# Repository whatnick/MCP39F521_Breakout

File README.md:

# MCP39F521 Breakout PCB

This is a basic breakout PCB for the [MCP39F521](https://www.microchip.com/wwwproducts/en/MCP39F521)
ASIC from Microchip. This ASIC has ADC's and an embedded PIC microcontroller to perform high-accuracy
energy measurements. The ASIC can appear in upto 4 i2c addresses based on jumper settings. The breakout
board is usable with this [Arduino Library](https://github.com/upbeatlabs/drwattson/tree/master/Arduino/UpbeatLabs_MCP39F521)

## PCB Design

## PCB Availabilty

- [Tindie]()
- [PCBWay]()
- [Aisler]()
- [OSHPark]()

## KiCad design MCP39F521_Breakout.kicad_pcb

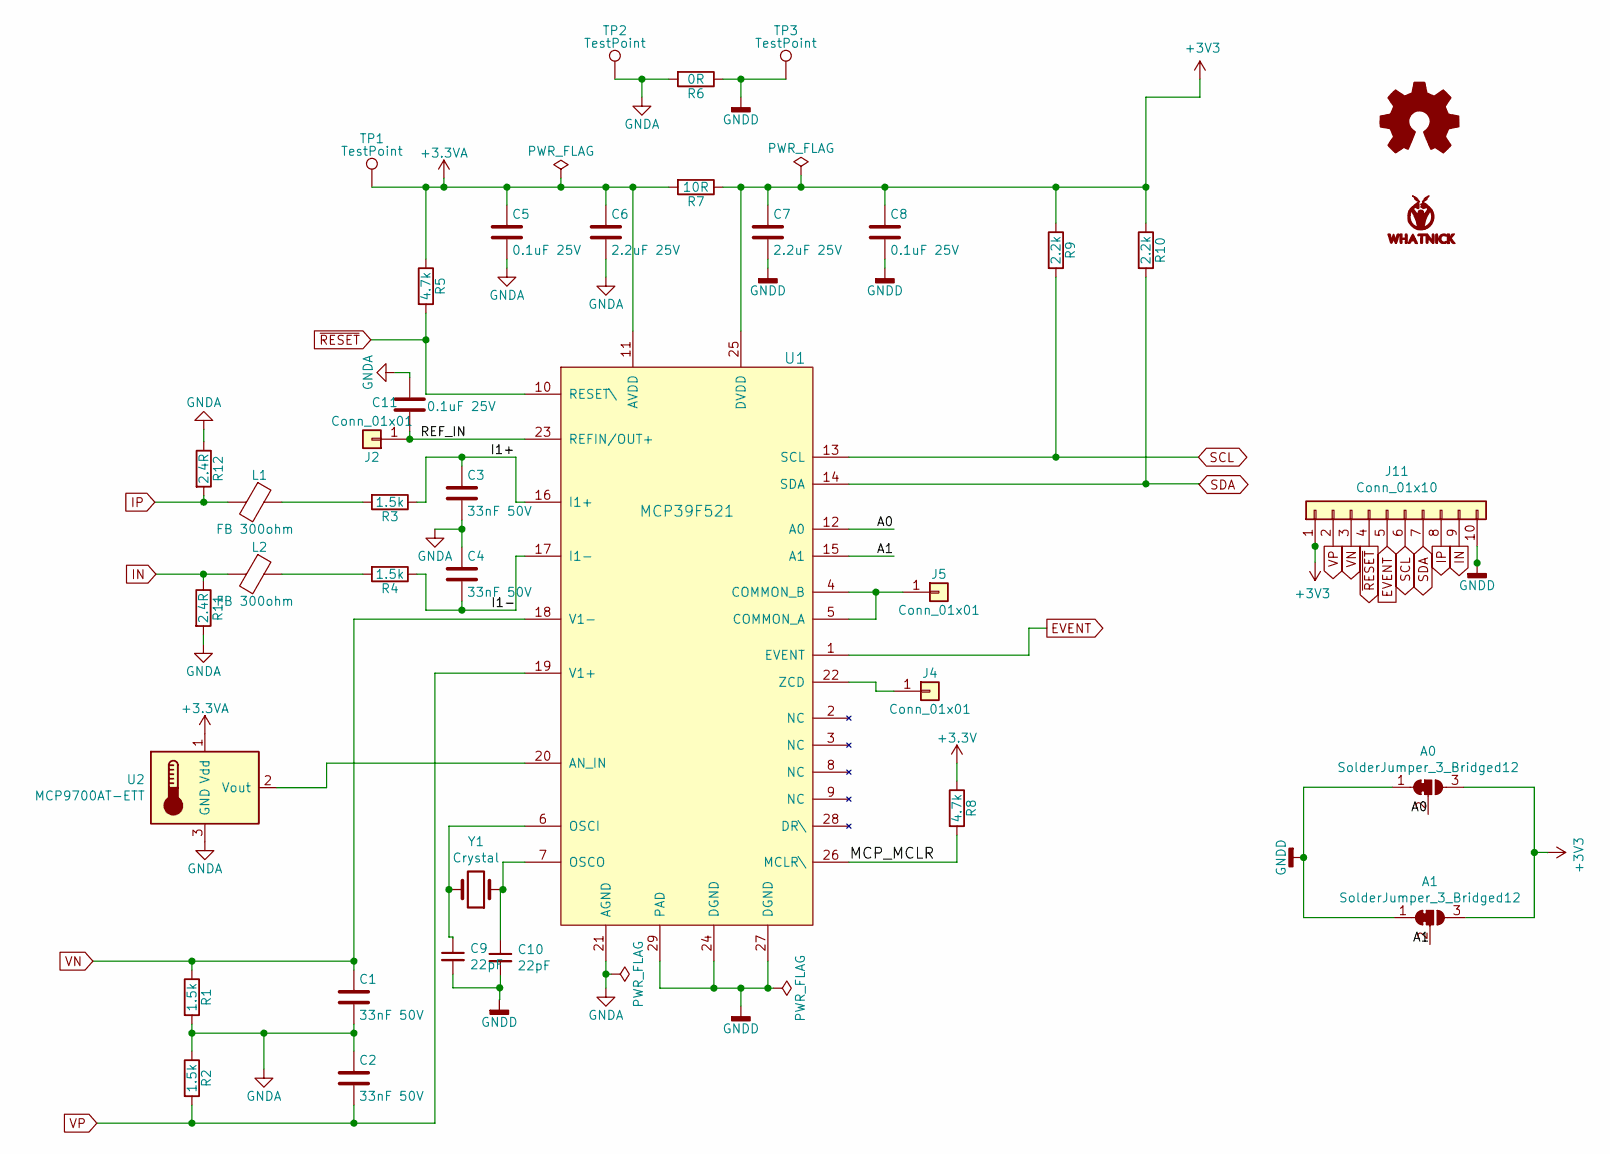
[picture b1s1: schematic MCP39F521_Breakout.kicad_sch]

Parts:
A0, A1: SolderJumper_3_Bridged12; SolderJumper-3_P1.3mm_Bridged12_Pad1.0x1.5mm
C1, C2, C3, C4: 33nF 50V; C_0603_1608Metric
C5, C8, C11: 0.1uF 25V; C_0603_1608Metric
C6, C7: 2.2uF 25V; C_0805_2012Metric
C9, C10: 22pF; C_0603_1608Metric
J2, J4, J5: Conn_01x01; TestPoint_Pad_1.5x1.5mm
J11: Conn_01x10; PinHeader_1x10_P2.54mm_Vertical
L1, L2: FB 300ohm; L_0603_1608Metric
LOGO1: Logo_Open_Hardware_Small; OSHW-Logo2_7.3x6mm_SilkScreen
LOGO2: LOGO; Whatnick_logo
R1, R2, R3, R4: 1.5k; R_0603_1608Metric
R5, R8: 4.7k; R_0603_1608Metric
R6: 0R; R_0603_1608Metric
R7: 10R; R_0603_1608Metric
R9, R10: 2.2k; R_0603_1608Metric
R11, R12: 2.4R; R_0603_1608Metric
TP1, TP2, TP3: TestPoint; TestPoint_Pad_1.5x1.5mm
U1: MCP39F521; QFN-28-1EP_5x5mm_P0.5mm_EP3.35x3.35mm
U2: MCP9700AT-ETT; SOT-23
Y1: Crystal; Crystal_SMD_HC49-SD

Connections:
+3.3VA: C5.1, C6.1, R5.1, R7.2, TP1.1, U1.11 (AVDD), U2.1 (Vdd)
/A0: A0.2 (C), U1.12 (A0)
/A1: A1.2 (C), U1.15 (A1)
/I1+: C3.1, R3.1, U1.16 (I1+)
/I1-: C4.2, R4.1, U1.17 (I1-)
/MCP_MCLR: R8.2, U1.26 (MCLR\)
/REF_IN: C11.2, J2.1, U1.23 (REFIN/OUT+)
EVENT: J11.5, U1.1 (EVENT)
GNDA: C1.2, C2.1, C3.2, C4.1, C5.2, C6.2, C11.1, R1.2, R2.1, R6.2, R11.2, R12.1, TP2.1, U1.21 (AGND), U2.3 (GND)
GNDD: A0.1 (A), A1.1 (A), C7.2, C8.2, C9.2, C10.2, J11.10, R6.1, TP3.1, U1.24 (DGND), U1.27 (DGND), U1.29 (PAD)
IN: J11.9, L2.2, R11.1
IP: J11.8, L1.2, R12.2
unnamed: C9.1, U1.6 (OSCI), Y1.2
unnamed: C10.1, U1.7 (OSCO), Y1.1
unnamed: J4.1, U1.22 (ZCD)
unnamed: J5.1, U1.4 (COMMON_B), U1.5 (COMMON_A)
unnamed: L1.1, R3.2
unnamed: L2.1, R4.2
unnamed: U1.20 (AN_IN), U2.2 (Vout)
SCL: J11.6, R9.2, U1.13 (SCL)
SDA: J11.7, R10.2, U1.14 (SDA)
VN: C1.1, J11.3, R1.1, U1.18 (V1-)
VP: C2.2, J11.2, R2.2, U1.19 (V1+)
~RESET: J11.4, R5.2, U1.10 (RESET\)

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
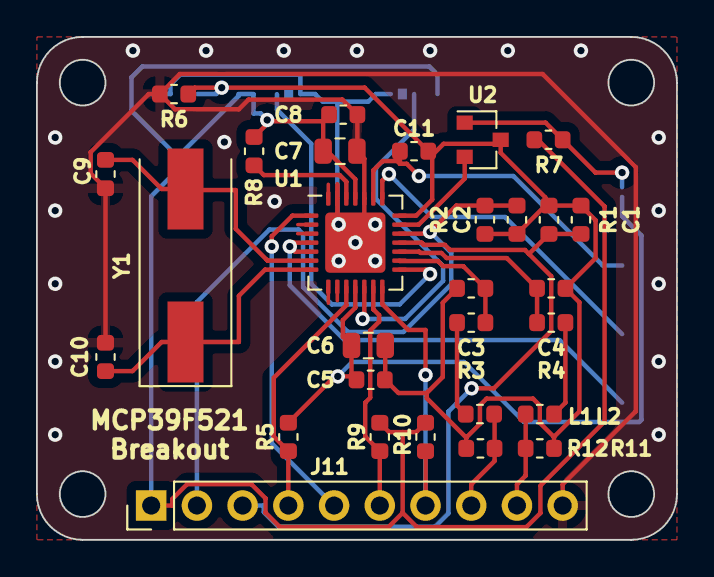
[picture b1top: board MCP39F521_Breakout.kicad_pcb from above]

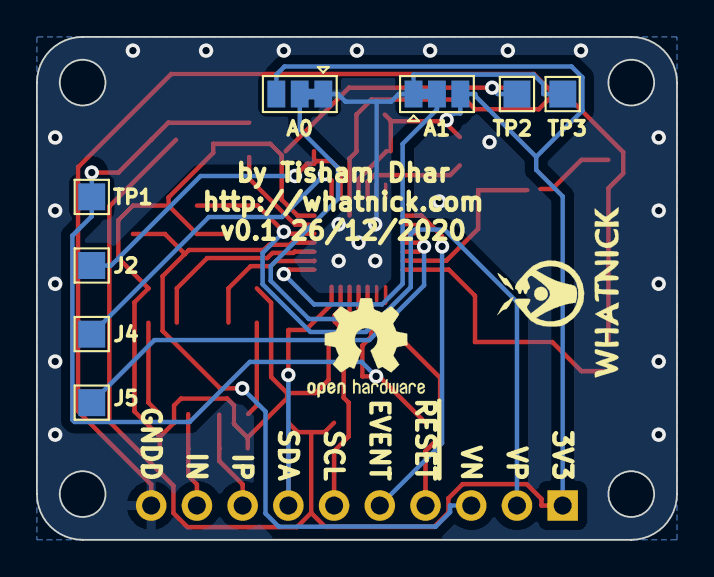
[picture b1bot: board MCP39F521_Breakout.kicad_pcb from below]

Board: 2 copper layers, 35.6 x 27.9 mm, 39 parts (10 on the bottom side), 25 nets.

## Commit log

2020-12-25 Merry Christmas
2020-12-25 More wiring
2020-12-25 Add address jumpers
2020-12-25 Cleanup copy-pasted symbols and perform initial autoroute
2020-12-25 Clean-up initial route and setup net-classes
2020-12-26 Ground planes and vias
2020-12-26 Clean up silk screen
2020-12-26 Create gerbers and swap to non-via footprint
2021-01-30 Updated BOM
2021-01-30 Removed temp xlsx
2021-01-30 Add docs
2021-08-14 Add footprint Positions
2021-08-15 Regenerate Gerbers
2024-12-28 Update to v7 and add elecrow BOM
